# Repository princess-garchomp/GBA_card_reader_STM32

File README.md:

In high school I had this idea of a thing I wanted to build. I wanted to make a thing that got roms out of GBA cartridges. 
I had no idea what knowledge I needed to gain to be able to execute on it. two degrees and three employers latter I knew enough to start this project. 
at this point, people have figured out this problem almost completely. but I still wanted to do it myself. 

I got my solution to the point of reading data out of the roms but then lost intereset, I had completed most of what I wanted to. 
because this problem has been solved by others, I did not need to get funcitong game files just some meaningfull data indicating my sytem worked.

partly I gave up to spend time looking for a new job.
now that I am not on the search for a better job, I am going to re-start this project. 

inital commits are what I found on my computer that I think were relevant. there may be more.

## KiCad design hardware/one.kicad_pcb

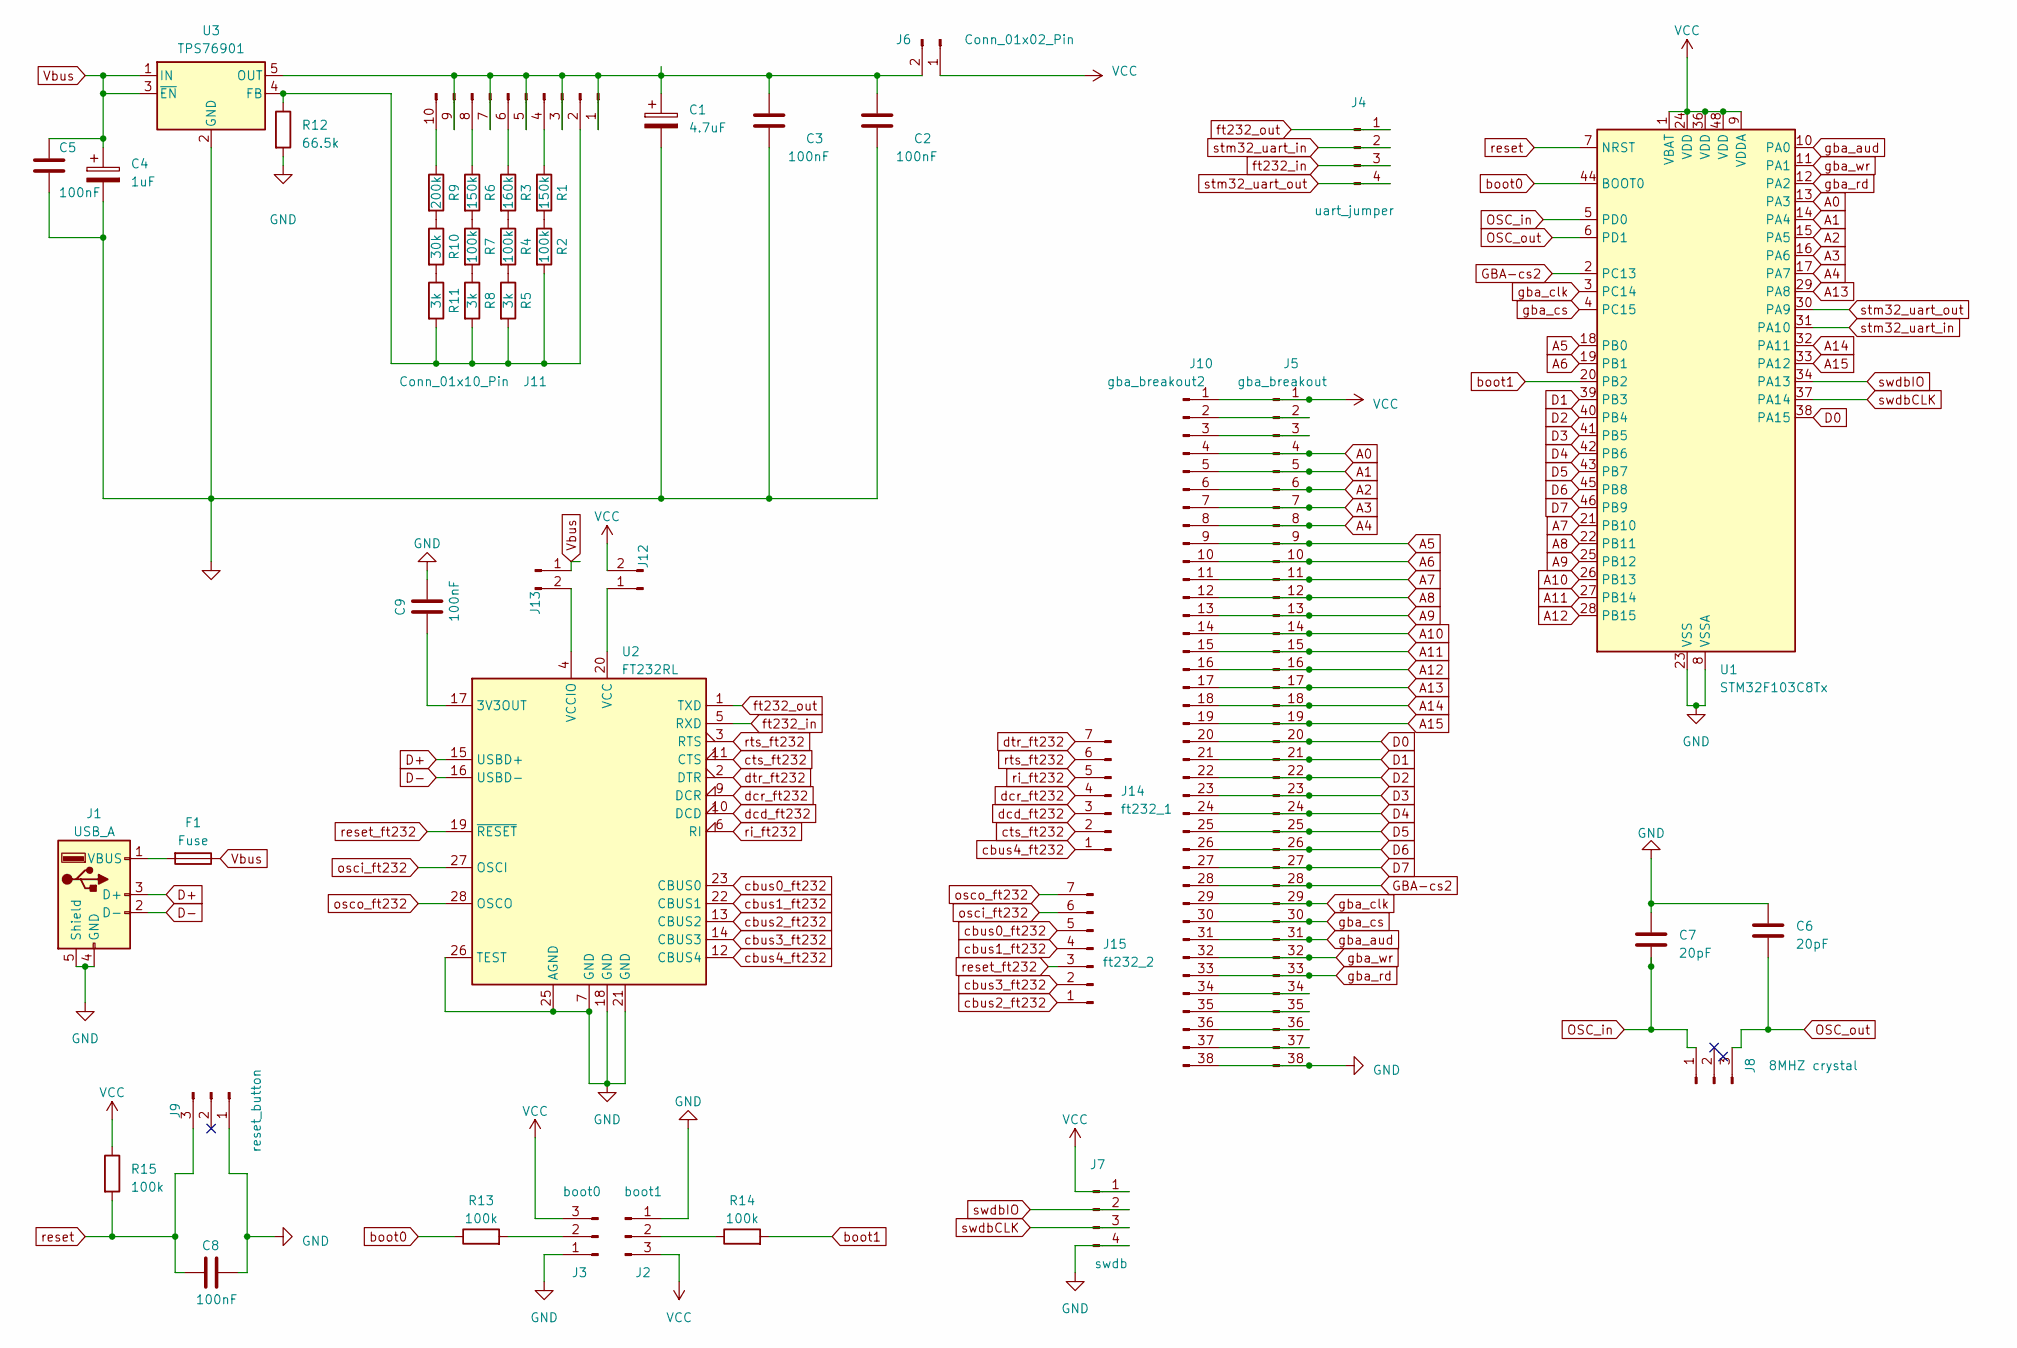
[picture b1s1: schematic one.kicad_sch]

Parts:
C1: 4.7uF; CP_EIA-3528-21_Kemet-B; LCSC C918865
C2, C3, C5, C8, C9: 100nF; C_0402_1005Metric; LCSC C338032
C4: 1uF; CP_EIA-3216-18_Kemet-A; LCSC C116269
C6, C7: 20pF; C_0402_1005Metric; LCSC C882568
F1: Fuse; Fuse_1206_3216Metric; LCSC C2836286
J1: USB_A; USB_A_Molex_67643_Horizontal
J2: boot1; PinSocket_1x03_P2.54mm_Vertical
J3: boot0; PinSocket_1x03_P2.54mm_Vertical
J4: uart_jumper; PinSocket_1x04_P2.54mm_Vertical
J5: gba_breakout; PinHeader_1x38_P2.54mm_Vertical
J6, J12, J13: Conn_01x02_Pin; PinHeader_1x02_P2.54mm_Vertical
J7: swdb; PinSocket_1x04_P2.54mm_Vertical
J8: 8MHZ crystal; PinSocket_1x03_P2.54mm_Vertical
J9: reset_button; PinSocket_1x03_P2.54mm_Vertical
J10: gba_breakout2; PinHeader_1x38_P2.54mm_Vertical
J11: Conn_01x10_Pin; PinSocket_1x10_P2.54mm_Vertical
J14: ft232_1; PinSocket_1x07_P2.54mm_Vertical
J15: ft232_2; PinSocket_1x07_P2.54mm_Vertical
R1, R6: 150k; R_0402_1005Metric; LCSC C429049
R2, R4, R7, R13, R14, R15: 100k; R_0402_1005Metric; LCSC C279979
R3: 160k; R_0402_1005Metric; LCSC C423115
R5, R8, R11: 3k; R_0402_1005Metric; LCSC C144761
R9: 200k; R_0402_1005Metric; LCSC C208822
R10: 30k; R_0402_1005Metric; LCSC C352437
R12: 66.5k; R_0402_1005Metric; LCSC C227185
U1: STM32F103C8Tx; LQFP-48_7x7mm_P0.5mm; LCSC C8734
U2: FT232RL; SSOP-28_5.3x10.2mm_P0.65mm; LCSC C8690
U3: TPS76901; SOT-23-5; LCSC C13997

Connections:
A0: J5.4, J10.4, U1.13 (PA3)
A1: J5.5, J10.5, U1.14 (PA4)
A2: J5.6, J10.6, U1.15 (PA5)
A3: J5.7, J10.7, U1.16 (PA6)
A4: J5.8, J10.8, U1.17 (PA7)
A5: J5.9, J10.9, U1.18 (PB0)
A6: J5.10, J10.10, U1.19 (PB1)
A7: J5.11, J10.11, U1.21 (PB10)
A8: J5.12, J10.12, U1.22 (PB11)
A9: J5.13, J10.13, U1.25 (PB12)
A10: J5.14, J10.14, U1.26 (PB13)
A11: J5.15, J10.15, U1.27 (PB14)
A12: J5.16, J10.16, U1.28 (PB15)
A13: J5.17, J10.17, U1.29 (PA8)
A14: J5.18, J10.18, U1.32 (PA11)
A15: J5.19, J10.19, U1.33 (PA12)
D0: J5.20, J10.20, U1.38 (PA15)
D1: J5.21, J10.21, U1.39 (PB3)
D2: J5.22, J10.22, U1.40 (PB4)
D3: J5.23, J10.23, U1.41 (PB5)
D4: J5.24, J10.24, U1.42 (PB6)
D5: J5.25, J10.25, U1.43 (PB7)
D6: J5.26, J10.26, U1.45 (PB8)
D7: J5.27, J10.27, U1.46 (PB9)
D+: J1.3 (D+), U2.15 (USBD+)
D-: J1.2 (D-), U2.16 (USBD-)
GBA-cs2: J5.28, J10.28, U1.2 (PC13)
GND: C1.2, C2.2, C3.2, C4.2, C5.2, C6.1, C7.1, C8.2, C9.2, J1.4 (GND), J1.5 (Shield), J2.1, J3.1, J5.38, J7.4, J9.1, J10.38, R12.2, U1.8 (VSSA), U1.23 (VSS), U1.35 (VSS), U1.47 (VSS), U2.7 (GND), U2.18 (GND), U2.21 (GND), U2.25 (AGND), U2.26 (TEST), U3.2 (GND); also elsewhere on the board
unnamed: F1.2, J1.1 (VBUS)
unnamed: J2.2, R14.1
unnamed: J3.2, R13.2
unnamed: J5.2, J10.2
unnamed: J5.3, J10.3
unnamed: J5.34, J10.34
unnamed: J5.35, J10.35
unnamed: J5.36, J10.36
unnamed: J5.37, J10.37
unnamed 37: C1.1, C2.1, C3.1, J6.2, J11.1, J11.3, J11.5, J11.7, J11.9, U3.5 (OUT); also elsewhere on the board
unnamed: J11.2, R2.2, R5.2, R8.2, R11.2, R12.1, U3.4 (FB)
unnamed: J11.4, R1.1
unnamed: J11.6, R3.1
unnamed: J11.8, R6.1
unnamed: J11.10, R9.1
unnamed: J12.1, U2.20 (VCC)
unnamed: J13.2, U2.4 (VCCIO)
unnamed: R1.2, R2.1
unnamed: R3.2, R4.1
unnamed: R4.2, R5.1
unnamed: R6.2, R7.1
unnamed: R7.2, R8.1
unnamed: R9.2, R10.1
unnamed: R10.2, R11.1
unnamed: C9.1, U2.17 (3V3OUT)
OSC_in: C7.2, J8.1, U1.5 (PD0)
OSC_out: C6.2, J8.3, U1.6 (PD1)
VCC: J2.3, J3.3, J5.1, J6.1, J7.1, J10.1, J12.2, R15.1, U1.1 (VBAT), U1.9 (VDDA), U1.24 (VDD), U1.36 (VDD), U1.48 (VDD); also elsewhere on the board
Vbus: C4.1, C5.1, F1.1, J13.1, U3.1 (IN), U3.3 (~EN)
boot0: R13.1, U1.44 (BOOT0)
boot1: R14.2, U1.20 (PB2)
cbus0_ft232: J15.5, U2.23 (CBUS0)
cbus1_ft232: J15.4, U2.22 (CBUS1)
cbus2_ft232: J15.1, U2.13 (CBUS2)
cbus3_ft232: J15.2, U2.14 (CBUS3)
cbus4_ft232: J14.1, U2.12 (CBUS4)
cts_ft232: J14.2, U2.11 (CTS)
dcd_ft232: J14.3, U2.10 (DCD)
dcr_ft232: J14.4, U2.9 (DCR)
dtr_ft232: J14.7, U2.2 (DTR)
ft232_in: J4.3, U2.5 (RXD)
ft232_out: J4.1, U2.1 (TXD)
gba_aud: J5.31, J10.31, U1.10 (PA0)
gba_clk: J5.29, J10.29, U1.3 (PC14)
gba_cs: J5.30, J10.30, U1.4 (PC15)
gba_rd: J5.33, J10.33, U1.12 (PA2)
gba_wr: J5.32, J10.32, U1.11 (PA1)
osci_ft232: J15.6, U2.27 (OSCI)
osco_ft232: J15.7, U2.28 (OSCO)
reset: C8.1, J9.3, R15.2, U1.7 (NRST); also elsewhere on the board
reset_ft232: J15.3, U2.19 (~RESET)
ri_ft232: J14.5, U2.6 (RI)
rts_ft232: J14.6, U2.3 (RTS)
stm32_uart_in: J4.2, U1.31 (PA10)
stm32_uart_out: J4.4, U1.30 (PA9)
swdbCLK: J7.3, U1.37 (PA14)
swdbIO: J7.2, U1.34 (PA13)

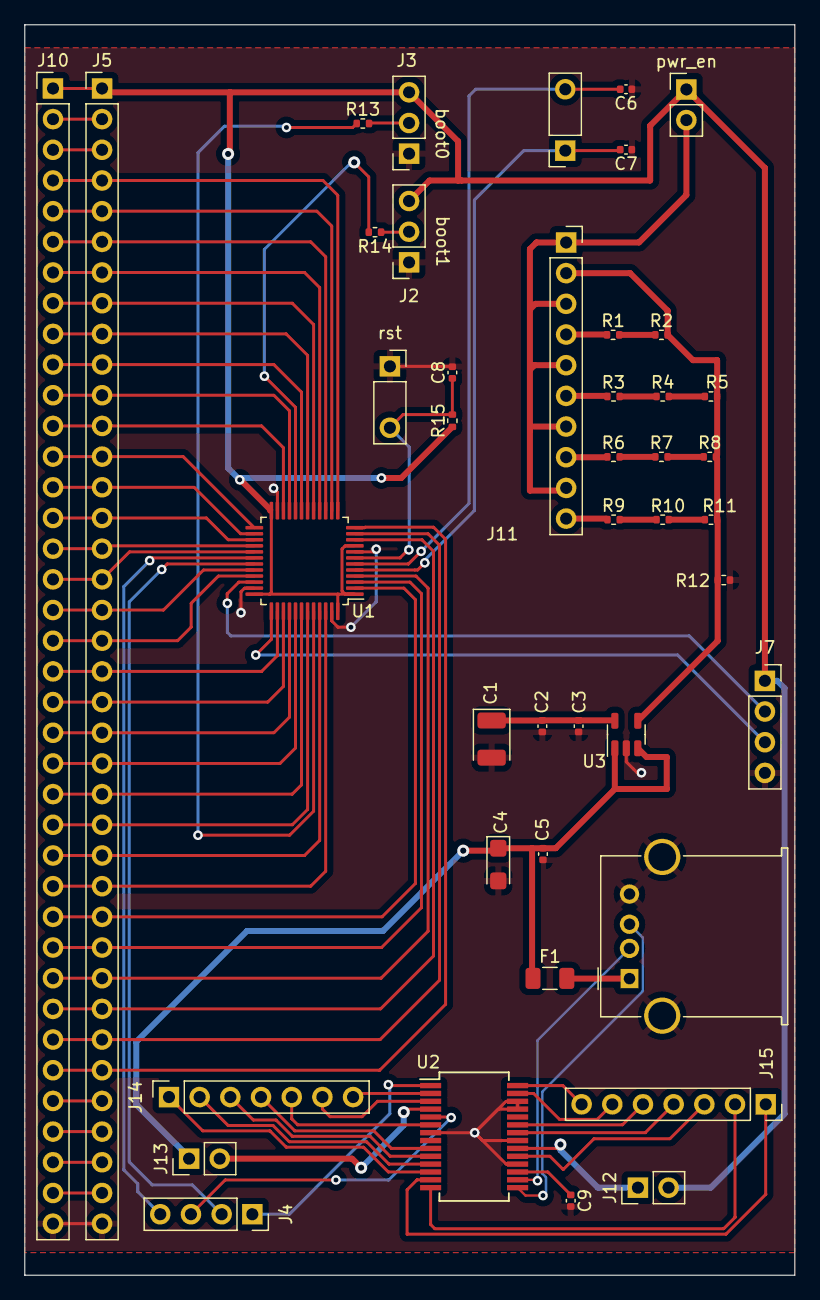
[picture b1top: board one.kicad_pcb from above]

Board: 2 copper layers, 63.8 x 103.5 mm, 43 parts (0 on the bottom side), 85 nets.

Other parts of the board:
pwr_en: Conn_01x02_Pin; PinHeader_1x02_P2.54mm_Vertical
rst: reset_button; PinSocket_1x03_P2.54mm_Vertical

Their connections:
GND: rst.1; also elsewhere on the board
unnamed 37: pwr_en.2; also elsewhere on the board
VCC: pwr_en.1; also elsewhere on the board
reset: rst.3; also elsewhere on the board

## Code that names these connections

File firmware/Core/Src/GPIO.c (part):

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
//all following 24 pins are used to write an address to the rom
//only pins A0 to A15 (16 pins) are data output by the rom after writting an address to it
//A0		PA3				CRL
//A1		PA4				CRL
//A2		PA5				CRL
//A3		PA6				CRL
//A4		PA7				CRL
//A5		PB0				CRL
//A6		PB1				CRL
//A7		PB10			CRH
//A8		PB11			CRH
//A9		PB12			CRH
//A10		PB13			CRH
//A11		PB14			CRH
//A12		PB15			CRH
//A13		PA8				CRH
//A14		PA11			CRH
//A15		PA12			CRH
//D0		PA15			CRH////////////////////replaced wiht A0. also used for the jtag interface....
//D1		PB3				CRL////////////////////replaced with PB2. PB3 is used for the jtag interface
//D2		PB4				CRL////////////////////replaced with PC13. PB4 is also used for the jtag interface...
//D3		PB5				CRL
//D4		PB6				CRL
//D5		PB7				CRL
//D6		PB8				CRH
//D7		PB9				CRH



////////////////////////////////////////////////////////////////////////
//masks/defines for the contorl pins that I have left

//GBA_CLK PC14
//GBA_CS  PC15
//GBA_WR  PA1
//GNA_RD  PA2

//this is the config we are using to output to the cart
//#define CRX_PUSH_PULL_OUTPUT_50_MHZ	(CNF_OUTPUT_PUSH_PULL|MODE_SPEED_50MHZ)//this is 4 pits long
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
void gpio_pin_one_output_config(void)
{
	//intent: led cathoed in to pa12 and led annoed into gnd
	//micro pin33(pa12), jumper pin 19 (A15)
	//enable the gpioA clokc
	RCC->APB2ENR |= RCC_APB2ENR_IOPAEN;//enalbe clock source

	//pA12 is in the CRH, not the CRL register
	//CHR resets at value 0x44444444, if we are ORing values into it we need to do a reset.
	GPIOA->CRH = 0;
	GPIOA->CRH |= (CNF_OUTPUT_PUSH_PULL<<PA12_CNF_OFFSET);//cnf1/cnf0. //push_pull
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void gpio_pin_two_input_config(void)
{
	//intent is to connect a push button between this pin and gnd. on button push the IDR will be a vale of 1
	//micro pin 12 (pa2), jumper pin 33 (GBA_RD)
	RCC->APB2ENR |= RCC_APB2ENR_IOPAEN;//enable clock source

	//pa2 is the CRL register not the CRH register
	//CHL resets at value 0x44444444, if we are ORing values into it we need to do a reset.
	GPIOA->CRL = 0;
	GPIOA->CRL |= (CNF_INPUT_PULL_UP<<PA2_CNF_OFFSET);//cnf1/cnf0. //push_pull
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
	//then I cant debug...
	//also I may have bricked a board. I cannot program it at the moment.
	//we need to disable the JTAG interface so pin PB3 will work.
	 /*RCC->APB2ENR |= RCC_APB2ENR_AFIOEN;
	AFIO->MAPR &= ~(AFIO_MAPR_SWJ_CFG_Msk);
	AFIO->MAPR |= AFIO_MAPR_SWJ_CFG_2;*/
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
void set_cart_rom_pins_input()
{
	//clear port A CRL bits for PA3 to PA7.
	GPIOA->CRL &= ~(CRL_A_IO_MASK);
	//set port A CRL as input with a pull down resistor to pins PA3 to PA7
	GPIOA->CRL |= (PORT_A_CRL_INPUT_CONFIG);
	//clear port A CRH bits for PA8, PA11, PA12
	GPIOA->CRH &= ~(CRH_A_IO_MASK);
	//set port A CRH as input with a pull down resistor to pins PA11,PA12
	GPIOA->CRH |= (PORT_A_CRH_INPUT_CONFIG);
	//set PINA ODR so that we have pull down resistors
	GPIOA->ODR & ~(PORT_A_ODR_INPUT_MASK);

	GPIOA->IDR = 0;

	//clear port B CRL bits for PB0, PB1, PB3 to PB7
	GPIOB->CRL &= ~(CRL_B_IO_MASK);
	//set port B CRL as input with a pull down resistor to pins PB0, PB1, PB3 to PB7
	GPIOB->CRL |= (PORT_B_CRL_INPUT_CONFIG);
	//clear port B CRH bits for PB8, PB9, PB10 to PB15
	GPIOB->CRH &= ~(CRH_B_IO_MASK);
	//set port B CRH as input with a pull down resistor to pins PB8, PB9, PB10 to PB15
	GPIOB->CRH |= (PORT_B_CRH_INPUT_CONFIG);
	//set PINB ODR so that we have pull down resistors
	GPIOB->ODR & ~(PORT_B_ODR_INPUT_MASK);
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}
void set_cart_rom_pins_output()
{
	//clear port A CRL bits for PA3 to PA7.
	GPIOA->CRL &= ~(CRL_A_IO_MASK);
	//set port A CRL as push pull output and 50MHZ to pins PA0 and PA3 to PA7
	GPIOA->CRL |= (PORT_A_CRL_OUTPUT_CONFIG);
	//clear port A CRH bits for PA8, PA11, PA12 and PA15
	GPIOA->CRH &= ~(CRH_A_IO_MASK);
	//set port A CRH as push pull output and 50MHZ to pins PA11,PA12
	GPIOA->CRH |= (PORT_A_CRH_OUTPUT_CONFIG);

	//clear port B CRL bits for PB0, PB1, PB2 adn PB4 to PB7
	GPIOB->CRL &= ~(CRL_B_IO_MASK);
	//set port B CRL as push pull output and 50MHZ to pins PB0, PB1, PB2 and PB4 to PB7
	GPIOB->CRL |= (PORT_B_CRL_OUTPUT_CONFIG);
	//clear port B CRH bits for PB8, PB9, PB10 to PB15
	GPIOB->CRH &= ~(CRH_B_IO_MASK);
	//set port B CRH as push pull output and 50MHZ to pins PB8, PB9, PB10 to PB15
	GPIOB->CRH |= (PORT_B_CRH_OUTPUT_CONFIG);

	//clear PORTC CRH bits for PC13
	GPIOC->CRH &= ~(CRH_C_IO_MASK);
	//seet CRH port C as push pull output and 50MHZ foor PC13
	GPIOC->CRH |= (PORT_C_CRH_OUTPUT_CONFIG);

	//clear ODR port A pins
	//clear PA3 to PA7, clear PA8, clear PA11 and PA12, clear PA0
	GPIOA->ODR &= ~(PORT_A_ODR_OUTPUT_MASK);

	//clear ODR port B pins
	//c;ear PB0 and PB1, clear PB10 to PB15, clear PB2 adn PB4 to PB9
	GPIOB->ODR &= ~(PORT_B_ODR_OUTPUT_MASK);

	//clear ODR port C pins, PC13
	GPIOC->ODR &= ~(PORT_C_ODR_OUTPUT_MASK);

}
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

	//set A0 to A4 on the cart
	//set pins PA3 to PA7 on the micro
	temp = (input & ~(0b11111111111111111111111111100000));//save bits in position form 0 to 4 from the input
	GPIOA->ODR |= (temp <<3);//left shift 3. get it to ODR positions for PA3 to PA7

	//set A5 to A6 on the cart
	//set pins PB0 to PB1 on the micro
	temp = (input & ~(0b11111111111111111111111110011111));//save bits in position form 5 and 6 from the input
	GPIOB->ODR |= (temp >>5);//right shift 5. get it to ODR positions for PB0 and PB1

	//set A7 to A12 on the cart
	//set pins PB10 to PB15 on the micro
	temp = (input & ~(0b11111111111111111110000001111111));//save bits in position form 7 and 12 from the input
	GPIOB->ODR |= (temp <<3);//left shift 4. get it to ODR positions for PB10 to PB15

	//set A13 on the cart
	//set pins PA8 on the micro
	temp = (input & ~(0b11111111111111111101111111111111));// save bit in position 13
	GPIOA->ODR |= (temp >>5);//right shift 5. get it to ODR position PA8

	//set A14 to A15 on the cart
	//set pins PA11 and PA12 on the micro
	temp = (input & ~(0b11111111111111110011111111111111));//save bits in positions 14 and 15
	GPIOA->ODR |= (temp >>3);//right shift 3. get it to ODR positions for PA11 and PA12

	//set D0 on the cart
	//set pins PA0 on the micro
	temp = (input & ~(0b11111111111111101111111111111111));//save bits in positions 16
	GPIOA->ODR |= (temp >>16);//right shit 1. get it to ODR position for PA0

	//D1 on the cart
	//set PB2 on the micro
	temp = (input & ~(0b11111111111111011111111111111111));//save bits in positions 17
	GPIOB->ODR |= (temp >>15);//right shift 15. get it to ODR positions PB2

	//set D2 cart
	//set pins PC13 on the micro
	temp = (input & ~(0b11111111111110111111111111111111));//save bits in positions 18
	GPIOC->ODR |= (temp >>5);//right shift 5. get it to ODR positions PC13

	//set D3 to D7 on the cart
	//set pins PB5 to PB9 on the micro
	temp = (input & ~(0b11111111000001111111111111111111));//save bits in positions 19 to 23
	GPIOB->ODR |= (temp >>14);//right shift 14. get it to ODR positions PB5 to PB9

}
uint16_t read_cart_rom(void)
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	//I did not realize how sloppy this would make my firmware.

	//				//(A15 |A14 |A13|A12 |A11 |A10 |A9  |A8  |A7  |A6 |A5 |A4 |A3 |A2 |A1 |A0)	//on the cart
	//return_value |= (PA12|PA11|PA8|PB15|PB14|PB13|PB12|PB11|PB10|PB0|PB1|PA7|PA6|PA5|PA4|PA3)	//on the micro
	uint16_t return_value = 0;
	uint16_t temp = 0;

	set_cart_rom_pins_input();

	temp = (GPIOA->IDR & ~(0b11111111111111111111111100000111));//save bits on pins PA3 to PA7
	return_value |= (temp>>3);//right shift by 3. put them in position A0 to A4

	temp = (GPIOB->IDR & ~(0b11111111111111111111111111111100));//save bits on pins PB0 and PB1
	return_value |= (temp<<5);//left shift by 5. put them in position A5 and A6

	temp = (GPIOB->IDR & ~(0b11111111111111110000001111111111));//save bits on pins PB10 ti PB15
	return_value |= (temp>>3);//right shift by 3. put them in positions A7 to A12

	temp = (GPIOA->IDR & ~(0b11111111111111111111111011111111));//save bits on pins PA8
	return_value |= (temp<<5);//left  shift by 5. put them in position A13

	temp = (GPIOA->IDR & ~(0b11111111111111111110011111111111));//save bits on pins PA11 and PA12
	return_value |= (temp<<3);//right shift by 3. put them in position A14 and A15

	return return_value;
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void init_control_pins()
{

 	//clear port A CRL bits for PA1 and PA2
 	GPIOA->CRL &= ~(CRL_A_CONTROL_PINS_IO_MASK);
 	//set port A CRL as push pull output and 50MHZ to pins PA1 and PA2
 	GPIOA->CRL |= (PORT_A_CONTROL_PINS_CRL_OUTPUT_CONFIG);

 	//clear port A CRL bits for PC14 adn PC15
 	GPIOC->CRH &= ~(CRH_C_CONTROL_PINS_IO_MASK);
 	//set port C CRL as push pull output and 50MHZ to pins PC14 and PC15
 	GPIOC->CRH |= (PORT_C_CONTROL_PINS_CRL_CRL_OUTPUT_CONFIG);

 	CLK_LOW();
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
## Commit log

2025-05-03 inital commit from work done in ~2023 I remember needing to do a lot of hardware mods to get things working I remember reading stuff out of the rom and having it print in a putty terminal I am not su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
2025-05-03 cleaning things up. the ugly way I was testing drivers is now put into its own C/H file.
2025-05-03 squash incomming...
2025-05-04 python talking to my board and getting most of the rom out, still debugging
2025-05-05 changes from 5_4_2025
2025-05-31 now reading roms. poorly. BUT it work so we design next
